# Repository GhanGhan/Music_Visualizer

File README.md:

# Overview      
The device receives an audio signal from a 3.5mm jack (i.e. a headphone jack) that is connected to any analog sound source. The audio signal is then separated into the **7 music frequency ranges** and their respective volumes' are then **displayed on 10 LED's using a decibel scale.**
The brightness of the LEDs and the maximum value of the decibal scale can be adjusted by the user by turning the potentiometers located at the bottom of the PCB shown in *Figure 1*!

***Figure 1: 3D View***
<!---
Hello world

<figure>
   
   <figcaption>**Figure 1: 3D View of Music Visualizer**</figcaption>
</figure>
--->

# Table of Contents
1. Summary of Functionaity
2. Operation Videos
3. Contained in Respository
4. Repository Structure
5. Folder & Design File Explanation
6. Generate Files for Fabrication
7. Current Issues
8. License
9. Acknowledgements

# Summary of Functionality
- Can change input source to a male or female jack using a slide switch as shown in *Figure 2*
- Can safely handle a differential input voltage signal of up to 32V
- Uses 6th order 60dB/decade active Butterworth filters to segment the signal into 7 spectrums
- Both the brightness of the LEDs and maximum scale voltage can be changed using logarithmic potentiometers
   - ** Due to how signal is processed by the filters, the maximum value of the volume scale is 3.5V
- 10 LEDS are used to display the volume of each spectrum as a percentage of the max value of the volume scale
   - 4 Blue LEDs     [4% : 12%]
   - 3 Yellow LEDS   [12% : 35%]
   - 3 Red LEDS      [35% : 100%]

***Figure 2: Block Diagaram of Signal, Power and Control Flow***

# Contained in Repository
- Spice design files (made using LTSpice)
- Schematic Capture and PCB layout (designed in KiCAD)
- Bill-of-Materials BOM
- Other important documents:
   - Sound characterization
   - Measured Frequency response
   - Docs related to properties of critical electrical components

# Operation Videos

# Repository Structure
```
├── Documents
│   ├── BOM_Final.xlsx
│   ├── LED Driver IC.xlsx
│   ├── MaxIoOfEachFilterStage.xlsx
│   ├── Measured_Frequency_Response.xlsx
│   ├── Sound_Characterization.xlsx
│   └── Trace width vs current.xlsx
├── Schematic_PCB/Music_Visualizer
│   ├── Music_Visualizer-backups
│   ├── Project Library
│   │   ├── Coloured_LEDs
│   │   │   ├── LED D5 - Blue_cutted.step
│   │   │   ├── LED D5 - Red_cutted.step
│   │   │   └── LED D5 - Yellow_cutted.step
│   │   ├── DC_Power_Jack
│   │   │   ├── CUI_DEVICES_PJ-079BH.step
│   │   │   ├── CUI_DEVICES.kicad_mod
│   │   │   └── PJ-079BH.lib
│   │   ├── Female_Audio_Jack
│   │   │   └── SJ-3523-SMT-TR--3DModel-STEP-56544.step
│   │   ├── LM3915_LED_Driver
│   │   │   └── LM3915N-1.lib
│   │   ├── Linear_Voltage_Regulator
│   │   │   ├── DIP794W45P254L959H508Q8.kicad_mod
│   │   │   └── LT1054IPE4.step
│   │   ├── PTV09A_Pot_Vertical
│   │   │   ├── PTV09.kicad_mod
│   │   │   └── PTV09A-4225F-B104.step
│   │   ├── PW_On_Off_Switch
│   │   │   ├── E-SWITCH_RR511D1121.kicad_mod
│   │   │   └── RR511D1121.step
│   │   ├── Slide_Switch
│   │   │   ├── OS102011MS2QN1.step
│   │   │   └── SW_OS102011MS2QN1.kicad_mod
│   │   ├── License.txt
│   │   └── how-to-import.htm
│   ├── Music_Visualizer.csv
│   ├── Music_Visualizer.kicad_pcb
│   ├── Music_Visualizer.kicad_prl
│   ├── Music_Visualizer.kicad_pro
│   ├── Music_Visualizer.kicad_sch
│   ├── Music_Visualizer.wbk
│   ├── Music_Visualizer.xml
│   ├── Power.kicad_sch
│   ├── fp-info-cache
│   ├── fp-lib-table
│   └── sym-lib-table
└── Simulated Circuits
    ├── Entire_Circuit 
    │   ├── Full_Visualizer.asc
    │   └── LM324.txt
    ├── Filters_With_LED_Drivers
    │   ├── FinalBassFilterWithLEDDriver.asc
    │   ├── FinalBrillianceFilterWithLEDDriver.asc
    │   ├── FinalLowMidrangeWithLEDDriver.asc
    │   ├── FinalMidrangeFilterWithLEDDriver.asc
    │   ├── FinalPresenceFilterWithLEDDriver.asc
    │   ├── FinalSubBassFilterWithLEDDriver.asc
    │   ├── FinalUpperMidrangeFilterWithLEDDriver.asc
    │   └── LM324.txt
    ├── LED_Driving
    │   ├── LM3915_Base_Circuit.asc
    │   ├── LM3915_Chain.asc
    │   ├── RhiControl_LTC1250.asc
    │   └── Voltage_Follower_Replacement.asc
    ├── Power
    │   ├── LT1054_Inverter_and_regulator.asc
    │   └── Reverse_Voltage_Protection.asc
    └── Spectrum_Filters
        ├── Final_Filters
        │   ├── FinalBassFilterBuf.asc
        │   ├── FinalBrillianceFilterBuf.asc
        │   ├── FinalLowMidrangeBuf.asc
        │   ├── FinalMidrangeFilterBuf.asc
        │   ├── FinalPresenceFilterBuf.asc
        │   ├── FinalSubBassFilterBuf.asc
        │   ├── FinalUpperMidrangeFilterBuf.asc
        │   └── LM324.txt
        ├── Ideal_Filters
        │   ├── BassFilterSK.asc
        │   ├── BrillianceFilterSK.asc
        │   ├── LowMidrangeSK.asc
        │   ├── MidrangeFilterSK.asc
        │   ├── PresenceFilterSK.asc
        │   ├── SubBassFilterSK.asc
        │   └── UpperMidrangeFilterSK.asc
        └── JsonFiles
            ├── Bass Filter.asc
            ├── Brilliance Filter.asc
            ├── Low-Midrange.asc
            ├── Midrange Filter.asc
            ├── Presence Filter.asc
            ├── Sub-Bass Filter.asc
            └── Upper-MidrangeFilter.asc
  ```
# Folder & Design File Explanation
## Documents
- **BOM_Final:** The project Bill-Of-Materials (BOM)
   - Shows all the components that were used, the quantity of each, the prices, model number and where they were sourced from
- **LED Driver IC:** Comparison of the simulated characteristics and values found from breadboarding
- **MaxIoOfEachFilterStage:** Maximum possible current being output by each op-amp of each stage of every filter
- **Sound Characterization:** Shows voltages that were outputted from the audio jack the device was tested on, bandwidth and corner frequency of each spectrum, and steps of the volume-meter
## Schematic_PCB\Music Visualizer (KiCad Folder)
- **Project_Library:** Contains nesseccary .step files (3D models), .lib files (schematic symbols) and/or .kicad_mod files (PCB footprint)  of the DC power jack, female audio jack, LED driver, -5V Inverter & Regulator, potentiometer, On/Off rocker switch switch and slide switch.
    - If any of the file types for any of the circuit elements is not included in the associated sub-folder of the 'Project Library then it is provided by the programs 'Global Library'.
- **Music_Visualizer.kicad_pcb:** PCB layout file for the entire project.
- **Music_Visualizer.kicad_sch:** Main schematic layout file.
    - Contains all 7 frequency spectrums based on the spice files in Simulated_Circuits\Spectrum_Filter\Final_Filter folder.
    - Contains the Audio input circuit (male and female connections where a slide switch is used to choose one or the other), the mounting holes, and op amp bypass capacitors.
    - Contains the Power.kicad_sch and LED_driver.kicad_sch schematics as well
    - **Power.kicad_sch:** Contians circuit for the the +5V regulator, circuit to connect to external power supply with with reverse voltage protection  and -5V Inverter/Regulator as shown in *Figure 3*, the latter 2 are based on the spice files in Simulatd_Circuits\Power.

***Figure 3: 9V & +/-5V Power Circuitry***

    - **Led_Driver.kicad_sch:** Contains the 7 LED drivers, LED brightness control and Rhi-Value Control Circuit based on the spice files in LED_Driving folder.
- **Music_Visualizer.kicad_pro:** Music Visualizer KiCad File.  When clicked it opens up a directory that allows you to access the PCB layout file and schematic layout file.
- Rest of the files are either self explanatory of support files for the KiCad program
## Simulated_Circuits
- **Entire Circuit\Full_Visualizer.asc:** A spice file that contains the 7 spectrum filters being driven by the input signal that contains a frequency from each of the spectrums.  Each of the filters is driving one of the ICs in the LM3915_Chain circuit.  Voltage dividers are used in place of potentiometers to model how turning their knobs allows for control of the LED brightness and scale of the volumeter.
    - **LM324.txt:** A text file that contains the 'macromodel' of the LM324 operational amplifier, allowing it to be used in spice files
- **Filters_With_LED_Drivers:** Contains a spice file for every spectrum filter that driving an LM3915_Base_Circuit.  Also contains an LM324.txt file.
- **LED_Driving:**
    - **LM3915_Base_Circuit.asc:** Contains an LM3915 (the led driver) IC connected to 10 LEDs as shown in *Figure 4*.  The IC is driven by a sinusoidal voltage source.  **Vref (Current reference pin)** is used to set the diode current to about 18mA using a grounded 674 ohm resistor.  It is powered by 9V, and **Vrhi (high-input reference-voltage)** is set to 3.5V.

***Figure 4: LED Driving Circuit Prototype***

    - **LM3915_Chain.asc:** Contains 7 LM3915_Base circuits all driven by the same input AC voltage and high-input reference voltage.  Instead of ground, the 674 ohm resistor of each LM3915_Base circuit is connected to a grounded 10kohm potentiometer.  Changing the resistance of the potentiometer allows one to adjust the current going through the LEDs of all of the LED drivers.
    - **RhiControl_LTC1250.asc:** Connects to the high-input reference voltage pin (*Rhi in Figure 4*) of the LED driver IC as shown in *Figure 5*.  R1 and R2 act as a potentiometer. A voltage follower is appended to the ouput of the 'potentiometer' because the average load voltage of the Vrhi pin is about 17.5kohm, when there are in parallel the equivalent reisistance is about 2.5kohm.  The voltage follower ensures that the voltage at the pins is is the same value as the output of the potentiometer.  This particular op-amp was chosen because it has a max input offset voltage of < |10uV|, this means that the voltage at the pin will always be within 10uV of the desired voltage.

***Figure 5: Volume Scale Range Control Circuit***
  
    - **Voltage_Follower_Replacement.asc:**  This is a common-collector circuit, a single transistor implementation of a current follower.  The 2N2222 transistor is used to replace the LTC1250 op-amp because it shorted the -5 and +5 terminals that it was being powered from.
- **Spectrum_Filters:**
    - **Final_Filters:** Folder contains the final filter design for the 7 spectrum filters; Sub-Bass, Bass, Low-Midrange, Midrange, Upper-Midrange, Presence and Brilliance.  Each filter is prepended with a voltage buffer to isolate themselves from the signal source.  This way the impedances of the filters do not affect each other.  Each filter also has a high-pass filter appended to it to prevent unintented activation of the LED driver due to the input-offset voltage of the LM324 op amps which can be as high as 7mV.  *Figure 6* displays the Sub-Bass filters, all of the spectrum filters have the same topology.
  
***Figure 6: Complete Sub-Base Filter**

         - Also the resistor values in the final design are slightly different from the "ideal version".  This is because those resistances need at least two resistors in series or parallel to be realized.  The nominal resistor values choses for the final design are within 1.5% of the ideal value.  It was determined that this did not have a significant effect on the frequency response. 
    - **Ideal_Filters:** Folder contains design for idealized implementation of the 7 spectrum filters.  In these LTSpice files ideal op-amps are being used and all of the resistor values match the values provided from the Analog Filter Wizard.
    - **JsonFiles:** The spectrum filters were designed using Analog Devices 'Analog Filter Wizard'.  Once you've inputted the specifications "Passband gain, corner frequency, bandwidth, stopband, center frequency, stages etc."  These are the saved specification files of the Analog filter Wizard for each filter.
         - The center frequency saved in these files are different from the actual center frequency of the filters because (for unidentified reasons) when the correct center frequency was inputted to wrong corner frequencies were outputed.  The center frequency contained in these files gives filters with the correct corner frequencies.

# Generate Files for Fabrication
- If you want to generate the Gerber and Drill files so that the project can be fabricated by a JLCPCB, follow the steps of this website: https://jlcpcb.com/help/article/16-How-to-generate-Gerber-and-Drill-files-in-KiCad-6

# Current Issues
- The last stage of the sub-bass filter generates a power 343Hz wave on its own that is so powerful it activates all of the associated LEDS.  
- The LT1054 op amp shorts the +5 and -5 power rails together and destroys itself in the process.  The is why it was replaced with a Common Collector circuit.

# License
- 
- This project is licensed under the [Creative Commons Attribution 3.0 Unported License](https://creativecommons.org/licenses/by/3.0/).
  
# Acknoledgments
- I would like to thank Snap EDA for providing me with the necessary step, kicad_mod and lib files.
- I would like to thank the YouTube Channel "Phil's Lab" for making videos that allowed me to easily learn to use KiCad 6.

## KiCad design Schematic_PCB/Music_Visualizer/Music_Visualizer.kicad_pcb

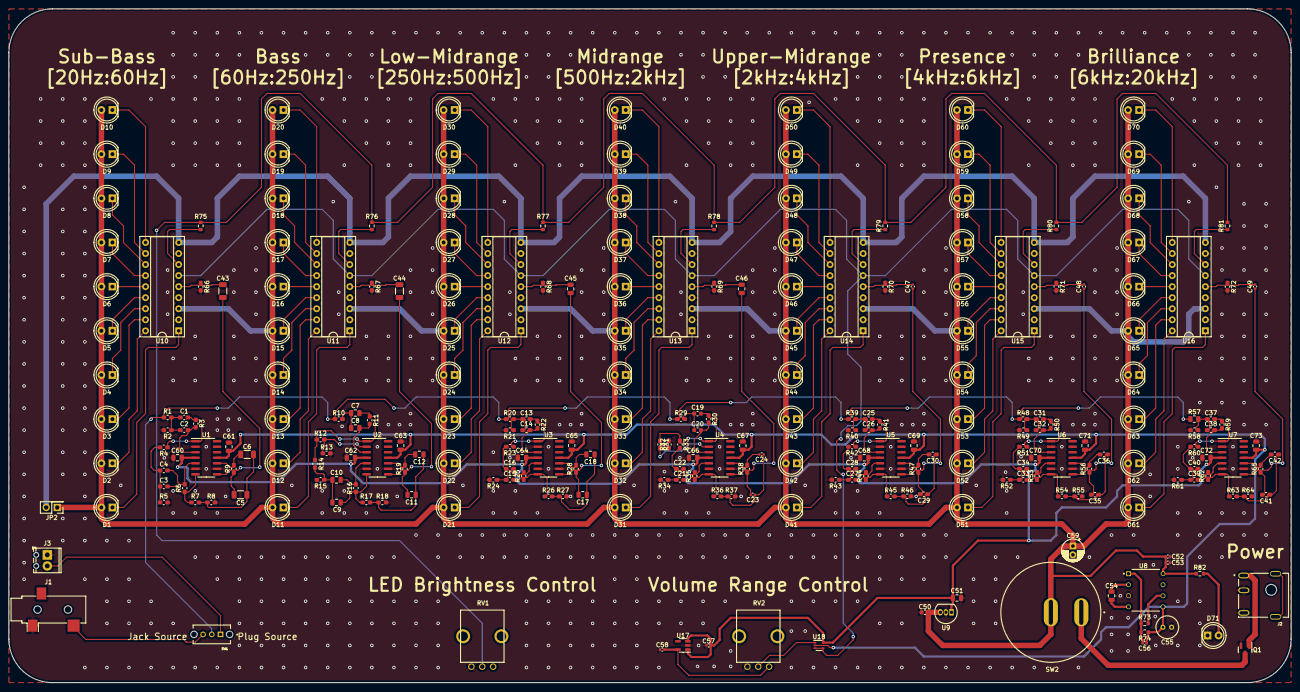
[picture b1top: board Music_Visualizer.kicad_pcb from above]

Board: 2 copper layers, 295.0 x 155.0 mm, 253 parts (0 on the bottom side), 169 nets.

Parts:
C1, C2: 47n; C_0603_1608Metric_Pad1.08x0.95mm_HandSolder
C3, C4: 27n; C_0603_1608Metric_Pad1.08x0.95mm_HandSolder
C5, C6: 75n; C_1206_3216Metric
C7, C8: 13n; C_0805_2012Metric
C9, C10: 6.8n; C_0805_2012Metric
C11, C12: 24n; C_0805_2012Metric
C13, C14: 4.7n; C_0603_1608Metric_Pad1.08x0.95mm_HandSolder
C15, C16: 3.3n; C_0603_1608Metric_Pad1.08x0.95mm_HandSolder
C17, C18: 6.2n; C_0805_2012Metric
C19, C20: 1.6n; C_0603_1608Metric
C21, C22, C25, C26, C27, C28, C29, C30, C31, C32, C33, C34, C35, C36, C37, C38, C39, C40, C41, C42: 1n; C_0603_1608Metric_Pad1.08x0.95mm_HandSolder
C23, C24: 3n; C_0402_1005Metric
C43, C44: 100u; C_1206_3216Metric
C45, C46, C54: 10u; C_0805_2012Metric
C47, C48, C49, C52, C53, C57, C58: 1u; C_0402_1005Metric
C50: 0.33uF; C_0603_1608Metric
C51, C60, C61, C62, C63, C64, C65, C66, C67, C68, C69, C70, C71, C72, C73: 0.1uF; C_0805_2012Metric
C55: 100u; C_Radial_D5.0mm_H5.0mm_P2.00mm
C56: 0.002u; C_0402_1005Metric
C59: 10u; CP_Radial_D5.0mm_P2.00mm
D1, D2, D3, D4, D5, D6, D7, D8, D9, D10, D11, D12, D13, D14, D15, D16, D17, D18, D19, D20, D21, D22, D23, D24, D25, D26, D27, D28, D29, D30, D31, D32, D33, D34, D35, D36, D37, D38, D39, D40, D41, D42, D43, D44, D45, D46, D47, D48, D49, D50, D51, D52, D53, D54, D55, D56, D57, D58, D59, D60, D61, D62, D63, D64, D65, D66, D67, D68, D69, D70, D71: LED; LED_D5.0mm
J1: AudioJack3; Jack_3.5mm_CUI_SJ-3523-SMT_Horizontal
J2: PJ-079BH; CUI_PJ-079BH
J3: Screw_Terminal_01x02; TerminalBlock_Phoenix_MPT-0,5-2-2.54_1x02_P2.54mm_Horizontal
JP2: Jumper_2_Open; PinHeader_2x01_P2.54mm_Vertical
Q1: DMP2123LQ-7; SOT-23
R1: 84.5k; C_0603_1608Metric_Pad1.08x0.95mm_HandSolder
R2, R41, R50: 160k; C_0603_1608Metric_Pad1.08x0.95mm_HandSolder
R3: 169k; C_0603_1608Metric_Pad1.08x0.95mm_HandSolder
R4, R11, R65: 90.9k; C_0603_1608Metric_Pad1.08x0.95mm_HandSolder
R5, R62: 37.4k; C_0603_1608Metric_Pad1.08x0.95mm_HandSolder
R6: 402k; C_0603_1608Metric_Pad1.08x0.95mm_HandSolder
R7: 86.6k; C_0603_1608Metric_Pad1.08x0.95mm_HandSolder
R8: 35.7k; C_0603_1608Metric_Pad1.08x0.95mm_HandSolder
R9: 390k; C_0603_1608Metric_Pad1.08x0.95mm_HandSolder
R10: 110k; C_0603_1608Metric_Pad1.08x0.95mm_HandSolder
R12: 162k; C_0603_1608Metric_Pad1.08x0.95mm_HandSolder
R13: 118k; C_0603_1608Metric_Pad1.08x0.95mm_HandSolder
R14: 63.4k; C_0603_1608Metric_Pad1.08x0.95mm_HandSolder
R15: 62k; C_0603_1608Metric_Pad1.08x0.95mm_HandSolder
R16: 309k; C_0603_1608Metric_Pad1.08x0.95mm_HandSolder
R17: 68k; C_0603_1608Metric_Pad1.08x0.95mm_HandSolder
R18, R31, R36, R51: 66.5k; C_0603_1608Metric_Pad1.08x0.95mm_HandSolder
R19: 332k; C_0603_1608Metric_Pad1.08x0.95mm_HandSolder
R20: 137k; C_0603_1608Metric_Pad1.08x0.95mm_HandSolder
R21: 45.3k; C_0603_1608Metric_Pad1.08x0.95mm_HandSolder
R22, R35, R53: 270k; C_0603_1608Metric_Pad1.08x0.95mm_HandSolder
R23: 143k; C_0603_1608Metric_Pad1.08x0.95mm_HandSolder
R24: 19.1k; C_0603_1608Metric_Pad1.08x0.95mm_HandSolder
R25: 590k; C_0603_1608Metric_Pad1.08x0.95mm_HandSolder
R26: 140k; C_0603_1608Metric_Pad1.08x0.95mm_HandSolder
R27: 18.7k; C_0603_1608Metric_Pad1.08x0.95mm_HandSolder
R28: 576k; C_0603_1608Metric_Pad1.08x0.95mm_HandSolder
R29, R30: 100k; C_0603_1608Metric_Pad1.08x0.95mm_HandSolder
R32: 33.2k; C_0603_1608Metric_Pad1.08x0.95mm_HandSolder
R33: 56k; C_0603_1608Metric_Pad1.08x0.95mm_HandSolder
R34, R58: 48.7k; C_0603_1608Metric_Pad1.08x0.95mm_HandSolder
R37: 57.6k; C_0603_1608Metric_Pad1.08x0.95mm_HandSolder
R38: 324k; C_0603_1608Metric_Pad1.08x0.95mm_HandSolder
R39, R48: 78.7k; C_0603_1608Metric_Pad1.08x0.95mm_HandSolder
R40: 26.7k; C_0603_1608Metric_Pad1.08x0.95mm_HandSolder
R42: 59k; C_0603_1608Metric_Pad1.08x0.95mm_HandSolder
R43: 7.87k; C_0603_1608Metric_Pad1.08x0.95mm_HandSolder
R44: 243k; C_0603_1608Metric_Pad1.08x0.95mm_HandSolder
R45: 107k; C_0603_1608Metric_Pad1.08x0.95mm_HandSolder
R46: 14.7k; C_0603_1608Metric_Pad1.08x0.95mm_HandSolder
R47: 453k; C_0603_1608Metric_Pad1.08x0.95mm_HandSolder
R49: 7.32k; C_0603_1608Metric_Pad1.08x0.95mm_HandSolder
R52: 2.87k; C_0603_1608Metric_Pad1.08x0.95mm_HandSolder
R54: 95.3k; C_0603_1608Metric_Pad1.08x0.95mm_HandSolder
R55: 4.02k; C_0603_1608Metric_Pad1.08x0.95mm_HandSolder
R56: 383k; C_0603_1608Metric_Pad1.08x0.95mm_HandSolder
R57: 11.5k; R_0805_2012Metric
R59: 22.6k; C_0603_1608Metric_Pad1.08x0.95mm_HandSolder
R60: 8.06k; C_0603_1608Metric_Pad1.08x0.95mm_HandSolder
R61: 4.32k; C_0603_1608Metric_Pad1.08x0.95mm_HandSolder
R63: 19.6k; C_0603_1608Metric_Pad1.08x0.95mm_HandSolder
R64: 10.7k; C_0603_1608Metric_Pad1.08x0.95mm_HandSolder
R66, R67, R68, R69, R70, R71, R72: 1k; C_0603_1608Metric_Pad1.08x0.95mm_HandSolder
R73: 20k; R_0603_1608Metric
R74: 102k; R_0603_1608Metric
R75, R76, R77, R78, R79, R80, R81: 680; R_0603_1608Metric
R82: 330; R_0603_1608Metric
RV1: 10k_LED_Brightness_Pot; PTV09
RV2: 5k_Rhi_Adjuster; PTV09
SW1: SW_SPDT; SW_OS102011MS2QN1
SW2: SW_SPST; E-SWITCH_RR511D1121
U1, U2, U3, U4, U5, U6, U7: LM324; SOIC-14_3.9x8.7mm_P1.27mm
U8: LT1054; DIP794W45P254L959H508Q8
U9: MC78L05_TO92; TO-92_Inline
U10, U11, U12, U13, U14, U15, U16: LM3915N-1; DIP-18_W7.62mm_Socket
U17: NCP161ASN350T1G; SOT-23-5
U18: NCS333ASQ3T2G; SOT-353_SC-70-5

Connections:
+5V: C51.1, C57.1, C60.2, C62.2, C64.2, C66.2, C68.2, C70.2, C72.2, U1.4 (V+), U2.4 (V+), U3.4 (V+), U4.4 (V+), U5.4 (V+), U6.4 (V+), U7.4 (V+), U9.1 (VO), U17.1 (IN), U17.3 (EN), U18.5 (V+)
+9V: C50.1, C52.1, C53.1, C59.1, D1.2 (A), D2.2 (A), D3.2 (A), D4.2 (A), D5.2 (A), D6.2 (A), D7.2 (A), D8.2 (A), D9.2 (A), D10.2 (A), D11.2 (A), D12.2 (A), D13.2 (A), D14.2 (A), D15.2 (A), D16.2 (A), D17.2 (A), D18.2 (A), D19.2 (A), D20.2 (A), D21.2 (A), D22.2 (A), D23.2 (A), D24.2 (A), D25.2 (A), D26.2 (A), D27.2 (A), D28.2 (A), D29.2 (A), D30.2 (A), D31.2 (A), D32.2 (A), D33.2 (A), D34.2 (A), D35.2 (A), D36.2 (A), D37.2 (A), D38.2 (A), D39.2 (A), D40.2 (A), D41.2 (A), D42.2 (A), D43.2 (A), D44.2 (A), D45.2 (A), D46.2 (A), D47.2 (A), D48.2 (A), D49.2 (A), D50.2 (A), D51.2 (A), D52.2 (A), D53.2 (A), D54.2 (A), D55.2 (A), D56.2 (A), D57.2 (A), D58.2 (A), D59.2 (A), D60.2 (A), D61.2 (A), D62.2 (A), D63.2 (A), D64.2 (A), D65.2 (A), D66.2 (A), D67.2 (A), D68.2 (A), D69.2 (A), D70.2 (A), JP2.1 (A), R82.1, SW2.2 (B), U8.8 (V+), U9.3 (VI), U10.3 (V+), U11.3 (V+), U12.3 (V+), U13.3 (V+), U14.3 (V+), U15.3 (V+), U16.3 (V+)
-5V: C55.1, C56.1, C61.1, C63.1, C65.1, C67.1, C69.1, C71.1, C73.1, R74.1, U1.11 (V-), U2.11 (V-), U3.11 (V-), U4.11 (V-), U5.11 (V-), U6.11 (V-), U7.11 (V-), U8.5 (-VOUT), U18.2 (V-)
/Power/Power: J2.1, Q1.1 (D)
/Vsig_female: J1.T, SW1.3 (C)
/Vsig_male: J3.2, SW1.1 (A)
GND: C50.2, C51.2, C52.2, C53.2, C55.2, C57.2, C58.2, C59.2, C60.1, C61.2, C62.1, C63.2, C64.1, C65.2, C66.1, C67.2, C68.1, C69.2, C70.1, C71.2, C72.1, C73.2, D71.1 (K), J1.S, J2.2, J2.3, J3.1, Q1.2 (G), R2.2, R5.2, R8.2, R13.2, R15.2, R18.2, R21.2, R24.2, R27.2, R32.2, R34.2, R37.2, R40.2, R43.2, R46.2, R49.2, R52.2, R55.2, R58.2, R61.2, R64.2, R66.2, R67.2, R68.2, R69.2, R70.2, R71.2, R72.2, RV1.1, RV2.1, U1.2 (-), U1.6 (-), U1.9 (-), U2.6 (-), U2.9 (-), U3.2 (-), U3.6 (-), U3.9 (-), U4.6 (-), U4.9 (-), U5.2 (-), U5.6 (-), U5.9 (-), U6.2 (-), U6.6 (-), U6.9 (-), U7.2 (-), U7.6 (-), U7.9 (-), U8.3 (GND), U9.2 (GND), U10.2 (V-), U10.4 (RLO), U10.8 (REF_ADJ), U11.2 (V-), U11.4 (RLO), U11.8 (REF_ADJ), U12.2 (V-), U12.4 (RLO), U12.8 (REF_ADJ), U13.2 (V-), U13.4 (RLO), U13.8 (REF_ADJ), U14.2 (V-), U14.4 (RLO), U14.8 (REF_ADJ), U15.2 (V-), U15.4 (RLO), U15.8 (REF_ADJ), U16.2 (V-), U16.4 (RLO), U16.8 (REF_ADJ), U17.2 (GND)
LED_Brightness_Control: R75.2, R76.2, R77.2, R78.2, R79.2, R80.2, R81.2, RV1.2
Mode: JP2.2 (B), U10.9 (MODE), U11.9 (MODE), U12.9 (MODE), U13.9 (MODE), U14.9 (MODE), U15.9 (MODE), U16.9 (MODE)
unnamed: C1.1, C2.1, R1.2, R2.1
unnamed: C1.2, R3.1, R4.1, U1.1
unnamed: C2.2, R3.2, U1.3 (+)
unnamed: C3.1, C4.1, R4.2, R5.1
unnamed: C3.2, R6.1, R7.1, U1.7
unnamed: C4.2, R6.2, U1.5 (+)
unnamed: C5.1, C6.1, R7.2, R8.1
unnamed: C6.2, R9.2, U1.10 (+)
unnamed: C7.1, C8.1, R10.2
unnamed: C7.2, R11.1, R12.1, R14.1, U2.1
unnamed: C8.2, R11.2, U2.3 (+)
unnamed: C9.2, R16.1, R17.1, U2.7
unnamed: C9.1, C10.1, R14.2, R15.1
unnamed: C10.2, R16.2, U2.5 (+)
unnamed: C11.1, C12.1, R17.2, R18.1
unnamed: C11.2, C44.1, R19.1, U2.8
unnamed: C12.2, R19.2, U2.10 (+)
unnamed: C13.1, C14.1, R20.2, R21.1
unnamed: C13.2, R22.1, R23.1, U3.1
unnamed: C14.2, R22.2, U3.3 (+)
unnamed: C15.1, C16.1, R23.2, R24.1
unnamed: C15.2, R25.1, R26.1, U3.7
unnamed: C16.2, R25.2, U3.5 (+)
unnamed: C17.1, C18.1, R26.2, R27.1
unnamed: C17.2, C45.1, R28.1, U3.8
unnamed: C18.2, R28.2, U3.10 (+)
unnamed: C19.1, C20.1, R29.2
unnamed: C19.2, R30.1, R31.1, R33.1, U4.1
unnamed: C20.2, R30.2, U4.3 (+)
unnamed: C21.1, C22.1, R33.2, R34.1
unnamed: C21.2, R35.1, R36.1, U4.7
unnamed: C22.2, R35.2, U4.5 (+)
unnamed: C23.1, C24.1, R36.2, R37.1
unnamed: C23.2, C46.1, R38.1, U4.8
unnamed: C24.2, R38.2, U4.10 (+)
unnamed: C25.1, C26.1, R39.2, R40.1
unnamed: C25.2, R41.1, R42.1, U5.1
unnamed: C26.2, R41.2, U5.3 (+)
unnamed: C27.1, C28.1, R42.2, R43.1
unnamed: C27.2, R44.1, R45.1, U5.7
unnamed: C28.2, R44.2, U5.5 (+)
unnamed: C29.1, C30.1, R45.2, R46.1
unnamed: C29.2, C47.1, R47.1, U5.8
unnamed: C30.2, R47.2, U5.10 (+)
unnamed: C31.1, C32.1, R48.2, R49.1
unnamed: C31.2, R50.1, R51.1, U6.1
unnamed: C32.2, R50.2, U6.3 (+)
unnamed: C33.1, C34.1, R51.2, R52.1
unnamed: C33.2, R53.1, R54.1, U6.7
unnamed: C34.2, R53.2, U6.5 (+)
unnamed: C35.1, C36.1, R54.2, R55.1
unnamed: C35.2, C48.1, R56.1, U6.8
unnamed: C36.2, R56.2, U6.10 (+)
unnamed: C37.1, C38.1, R57.2, R58.1
unnamed: C37.2, R59.1, R60.1, U7.1
unnamed: C38.2, R59.2, U7.3 (+)
unnamed: C39.1, C40.1, R60.2, R61.1
unnamed: C39.2, R62.1, R63.1, U7.7
unnamed: C40.2, R62.2, U7.5 (+)
unnamed: C41.1, C42.1, R63.2, R64.1
unnamed: C41.2, C49.1, R65.1, U7.8
unnamed: C42.2, R65.2, U7.10 (+)
unnamed: C5.2, C43.1, R9.1, U1.8
unnamed: C54.1, U8.2 (CAP+)
unnamed: C54.2, U8.4 (CAP-)
unnamed: C56.2, R73.1, R74.2, U8.1 (FB/SHDN)
unnamed: C58.1, RV2.3, U17.5 (OUT)
unnamed: D1.1 (K), U10.1 (LED1_K)
unnamed: D2.1 (K), U10.18 (LED2_K)
unnamed: D3.1 (K), U10.17 (LED3_K)
unnamed: D4.1 (K), U10.16 (LED4_K)
unnamed: D5.1 (K), U10.15 (LED5_K)
unnamed: D6.1 (K), U10.14 (LED6_K)
unnamed: D7.1 (K), U10.13 (LED7_K)
unnamed: D8.1 (K), U10.12 (LED8_K)
unnamed: D9.1 (K), U10.11 (LED9_K)
unnamed: D10.1 (K), U10.10 (LED10_K)
unnamed: D11.1 (K), U11.1 (LED1_K)
unnamed: D12.1 (K), U11.18 (LED2_K)
unnamed: D13.1 (K), U11.17 (LED3_K)
unnamed: D14.1 (K), U11.16 (LED4_K)
unnamed: D15.1 (K), U11.15 (LED5_K)
unnamed: D16.1 (K), U11.14 (LED6_K)
unnamed: D17.1 (K), U11.13 (LED7_K)
unnamed: D18.1 (K), U11.12 (LED8_K)
unnamed: D19.1 (K), U11.11 (LED9_K)
unnamed: D20.1 (K), U11.10 (LED10_K)
unnamed: D21.1 (K), U12.1 (LED1_K)
unnamed: D22.1 (K), U12.18 (LED2_K)
unnamed: D23.1 (K), U12.17 (LED3_K)
unnamed: D24.1 (K), U12.16 (LED4_K)
unnamed: D25.1 (K), U12.15 (LED5_K)
unnamed: D26.1 (K), U12.14 (LED6_K)
unnamed: D27.1 (K), U12.13 (LED7_K)
unnamed: D28.1 (K), U12.12 (LED8_K)
unnamed: D29.1 (K), U12.11 (LED9_K)
unnamed: D30.1 (K), U12.10 (LED10_K)
unnamed: D31.1 (K), U13.1 (LED1_K)
unnamed: D32.1 (K), U13.18 (LED2_K)
unnamed: D33.1 (K), U13.17 (LED3_K)
unnamed: D34.1 (K), U13.16 (LED4_K)
unnamed: D35.1 (K), U13.15 (LED5_K)
unnamed: D36.1 (K), U13.14 (LED6_K)
unnamed: D37.1 (K), U13.13 (LED7_K)
unnamed: D38.1 (K), U13.12 (LED8_K)
unnamed: D39.1 (K), U13.11 (LED9_K)
unnamed: D40.1 (K), U13.10 (LED10_K)
unnamed: D41.1 (K), U14.1 (LED1_K)
unnamed: D42.1 (K), U14.18 (LED2_K)
unnamed: D43.1 (K), U14.17 (LED3_K)
unnamed: D44.1 (K), U14.16 (LED4_K)
unnamed: D45.1 (K), U14.15 (LED5_K)
unnamed: D46.1 (K), U14.14 (LED6_K)
unnamed: D47.1 (K), U14.13 (LED7_K)
unnamed: D48.1 (K), U14.12 (LED8_K)
unnamed: D49.1 (K), U14.11 (LED9_K)
unnamed: D50.1 (K), U14.10 (LED10_K)
unnamed: D51.1 (K), U15.1 (LED1_K)
unnamed: D52.1 (K), U15.18 (LED2_K)
unnamed: D53.1 (K), U15.17 (LED3_K)
unnamed: D54.1 (K), U15.16 (LED4_K)
unnamed: D55.1 (K), U15.15 (LED5_K)
unnamed: D56.1 (K), U15.14 (LED6_K)
unnamed: D57.1 (K), U15.13 (LED7_K)
unnamed: D58.1 (K), U15.12 (LED8_K)
unnamed: D59.1 (K), U15.11 (LED9_K)
unnamed: D60.1 (K), U15.10 (LED10_K)
unnamed: D61.1 (K), U16.1 (LED1_K)
unnamed: D62.1 (K), U16.18 (LED2_K)
unnamed: D63.1 (K), U16.17 (LED3_K)
unnamed: D64.1 (K), U16.16 (LED4_K)
unnamed: D65.1 (K), U16.15 (LED5_K)
unnamed: D66.1 (K), U16.14 (LED6_K)
unnamed: D67.1 (K), U16.13 (LED7_K)
unnamed: D68.1 (K), U16.12 (LED8_K)
unnamed: D69.1 (K), U16.11 (LED9_K)
unnamed: D70.1 (K), U16.10 (LED10_K)
unnamed: D71.2 (A), R82.2
unnamed: J2.S1 (SHIELD), J2.S2 (SHIELD)
unnamed: Q1.3 (S), SW2.1 (A)
unnamed: R12.2, R13.1, U2.2 (-)
unnamed: R31.2, R32.1, U4.2 (-)
unnamed: R73.2, U8.6 (VREF)
unnamed: R75.1, U10.7 (REF_OUT)
unnamed: R76.1, U11.7 (REF_OUT)
unnamed: R77.1, U12.7 (REF_OUT)
unnamed: R78.1, U13.7 (REF_OUT)
unnamed: R79.1, U14.7 (REF_OUT)
unnamed: R80.1, U15.7 (REF_OUT)
unnamed: R81.1, U16.7 (REF_OUT)
unnamed: RV2.2, U18.1 (+)
Rhi_Value: U10.6 (RHI), U11.6 (RHI), U12.6 (RHI), U13.6 (RHI), U14.6 (RHI), U15.6 (RHI), U16.6 (RHI), U18.3 (-), U18.4
VBass: C44.2, R67.1, U11.5 (SIG)
VBrilliance: C49.2, R72.1, U16.5 (SIG)
VLowerMidrange: C45.2, R68.1, U12.5 (SIG)
VMidrange: C46.2, R69.1, U13.5 (SIG)
VPresence: C48.2, R71.1, U15.5 (SIG)
VSubBass: C43.2, R66.1, U10.5 (SIG)
VUpperMidrange: C47.2, R70.1, U14.5 (SIG)
Vsig: R1.1, R10.1, R20.1, R29.1, R39.1, R48.1, R57.1, SW1.2 (B)

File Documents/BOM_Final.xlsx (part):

Comment | Designator | Footprint | Quantity | Digi-Key PN | MPN | Price | Total Price | Part Page
47n | C1,C2 | Capacitor_SMD:C_0603_1608Metric_Pad1.08x0.95mm_HandSolder | 2 | 1292-1445-1-ND | 0603B473J250CT | 0.1 | 0.2 | https://www.digikey.ca/en/products/detail/walsin-technology-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
24n | C11,C12 | Capacitor_SMD:C_0805_2012Metric | 2 | 478-10432-1-ND | 08051C243JAT2A | 0.43 | 0.86 | https://www.digikey.ca/en/products/detail/kyocera-avx/08051C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
4.7n | C13,C14 | Capacitor_SMD:C_0603_1608Metric_Pad1.08x0.95mm_HandSolder | 2 | 1292-1440-1-ND | 0603B472J500CT | 0.1 | 0.2 | https://www.digikey.ca/en/products/detail/walsin-technology-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
3.3n | C15,C16 | Capacitor_SMD:C_0603_1608Metric_Pad1.08x0.95mm_HandSolder | 2 | 1292-1521-1-ND | 0603N332J500CT | 0.1 | 0.2 | https://www.digikey.ca/en/products/detail/walsin-technology-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
6.2n | C17,C18 | Capacitor_SMD:C_0805_2012Metric | 2 | 490-1637-1-ND | GRM2195C1H622JA01D | 0.41 | 0.82 | https://www.digikey.ca/en/products/detail/murata-electronics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
1.6n | C19,C20 | Capacitor_SMD:C_0603_1608Metric_Pad1.08x0.95mm_HandSolder | 2 | 490-1456-1-ND | GRM1885C1H162JA01D | 0.18 | 0.36 | https://www.digikey.ca/en/products/detail/murata-electronics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
1n | C21,C22,C25,C26,C27,C28,C29,C30,C31,C32,C33,C34,C35,C36,C37,C38,C41,C42 | Capacitor_SMD:C_0603_1608Metric_Pad1.08x0.95mm_HandSolder | 18 | 1276-1091-1-ND | CL10C102JB8NNNC | 0.1 | 1.8 | https://www.digikey.ca/en/products/detail/samsung-electro-me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
3n | C23,C24 | Capacitor_SMD:C_0603_1608Metric_Pad1.08x0.95mm_HandSolder | 2 | 490-6384-1-ND | GRM1885C1H302JA01D | 0.11 | 0.22 | https://www.digikey.ca/en/products/detail/murata-electronics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
27n | C3,C4 | Capacitor_SMD:C_0603_1608Metric_Pad1.08x0.95mm_HandSolder | 2 | 478-KAF15AR71H273JMTR-ND | KAF15AR71H273JM | 0.18 | 0.36 | https://www.digikey.ca/en/products/detail/kyocera-avx/KAF15A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
820p | C39,C40 | Capacitor_SMD:C_0603_1608Metric_Pad1.08x0.95mm_HandSolder | 2 | 1292-1548-1-ND | 0603N821J500CT | 0.14000000000000001 | 0.28000000000000003 | https://www.digikey.ca/en/products/detail/walsin-technology-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
100u | C43,C44 | Capacitor_SMD:C_1206_3216Metric | 2 | 490-GRM31CD80J107MEA8KCT-ND | GRM31CD80J107MEA8K | 0.56000000000000005 | 1.1200000000000001 | https://www.digikey.ca/en/products/detail/murata-electronics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
10u | C45,C46,C54 | Capacitor_SMD:C_0805_2012Metric | 3 | 1276-1096-1-ND | CL21A106KOQNNNE | 0.14000000000000001 | 0.42000000000000004 | https://www.digikey.ca/en/products/detail/samsung-electro-me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
1u | C47,C48,C49,C52,C53,C57,C58 | Capacitor_SMD:C_0603_1608Metric_Pad1.08x0.95mm_HandSolder | 7 | 311-3485-1-ND | CC0603JRX7R7BB105 | 0.34 | 2.3800000000000003 | https://www.digikey.ca/en/products/detail/yageo/CC0603JRX7R7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
75n | C5,C6 | Capacitor_SMD:C_1206_3216Metric | 2 | 490-6506-1-ND | GRM31C5C1H753JA01L | 0.53 | 1.06 | https://www.digikey.ca/en/products/detail/murata-electronics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
0.33uF | C50 | Capacitor_SMD:C_0603_1608Metric_Pad1.08x0.95mm_HandSolder | 1 | 732-7992-1-ND | 885012206074 | 0.14000000000000001 | 0.14000000000000001 | https://www.digikey.ca/en/products/detail/w%C3%BCrth-elektro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
100u | C55 | Capacitor_THT:C_Radial_D5.0mm_H5.0mm_P2.00mm | 1 | 732-8598-1-ND | 860010372006 | 0.15 | 0.15 | https://www.digikey.ca/en/products/detail/w%C3%BCrth-elektro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
0.002u | C56 | Capacitor_SMD:C_0603_1608Metric_Pad1.08x0.95mm_HandSolder | 1 | 490-GCM1885C1H202JA16DCT-ND | GCM1885C1H202JA16D | 0.1 | 0.1 | https://www.digikey.ca/en/products/detail/murata-electronics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
10u | C59 | Capacitor_THT:CP_Radial_D5.0mm_P2.00mm | 1 | 732-8593-1-ND | 860010372001 | 0.14000000000000001 | 0.14000000000000001 | https://www.digikey.ca/en/products/detail/w%C3%BCrth-elektro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
0.1uF | C51,C60,C61,C62,C63,C64,C65,C66,C67,C68,C69,C70,C71,C72,C73 | Capacitor_SMD:C_0805_2012Metric | 15 | 1276-1099-1-ND | CL21B104KACNNNC | 0.14000000000000001 | 2.1 | https://www.digikey.ca/en/products/detail/samsung-electro-me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
13n | C7,C8 | Capacitor_SMD:C_0805_2012Metric | 2 | 490-12752-1-ND | GRM2195C1H133JA01D | 0.36 | 0.72 | https://www.digikey.ca/en/products/detail/murata-electronics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
6.8n | C9,C10 | Capacitor_SMD:C_0805_2012Metric | 2 | 399-C0805C682J5GEC7210CT-ND | C0805C682J5GEC7210 | 0.36 | 0.72 | https://www.digikey.ca/en/products/detail/kemet/C0805C682J5G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
LED | D1,D2,D3,D4,D5,D6,D7,D8,D9,D10,D11,D12,D13,D14,D15,D16,D17,D18,D19,D20,D21,D22,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 | LED_THT:LED_D5.0mm | 70 | N/A | N/A | 3.3180000000000001E-2 | 2.3226 | https://www.amazon.ca/gp/product/B07N2GVCYZ/ref=ppx_yo_dt_b_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
MountingHole | H1,H2,H3,H4 | MountingHole:MountingHole_3.2mm_M3 | 4 | N/A | N/A | N/A | 0 | N/A
AudioJack3 | J1 | Connector_Audio:Jack_3.5mm_CUI_SJ-3523-SMT_Horizontal | 1 | CP-3523SJCT-ND | SJ-3523-SMT-TR | 1.42 | 1.42 | https://www.digikey.ca/en/products/detail/cui-devices/SJ-352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
PJ-079BH | J2 | CUI_PJ-079BH | 1 | 102-5547-ND | PJ-079BH | 2.19 | 2.19 | https://www.digikey.ca/en/products/detail/cui-devices/PJ-079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
Screw_Terminal_01x02 | J3 | TerminalBlock_Phoenix:TerminalBlock_Phoenix_MPT-0,5-2-2.54_1x02_P2.54mm_Horizon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 | 1 | 952-2262-ND | M20-9990246 | 0.19 | 0.19 | https://www.digikey.ca/en/products/detail/harwin-inc/M20-999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
Jumper_2_Open | JP2 | Connector_PinHeader_2.54mm:PinHeader_2x01_P2.54mm_Vertical | 1 | DMP2123LQ-7DICT-ND | DMP2123LQ-7 | 0.8 | 0.8 | https://www.digikey.ca/en/products/detail/diodes-incorporate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
DMP2123LQ-7 | Q1 | Package_TO_SOT_SMD:SOT-23 | 1 | DMP2123LQ-7DICT-ND | DMP2123LQ-7 | 0.69 | 0.69 | https://www.digikey.ca/en/products/detail/diodes-incorporate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
84.5k | R1 | Resistor_SMD:R_0603_1608Metric_Pad0.98x0.95mm_HandSolder | 1 | 311-84.5KHRCT-ND | RC0603FR-0784K5L | 0.15 | 0.15 | https://www.digikey.ca/en/products/detail/yageo/RC0603FR-078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
110k | R10 | Resistor_SMD:R_0603_1608Metric_Pad0.98x0.95mm_HandSolder | 1 | 311-110KHRCT-ND | RC0603FR-07110KL | 0.15 | 0.15 | https://www.digikey.ca/en/products/detail/yageo/RC0603FR-071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
162k | R12 | Resistor_SMD:R_0603_1608Metric_Pad0.98x0.95mm_HandSolder | 1 | 311-162KHRCT-ND | RC0603FR-07162KL | 0.15 | 0.15 | https://www.digikey.ca/en/products/detail/yageo/RC0603FR-071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
118k | R13 | Resistor_SMD:R_0603_1608Metric_Pad0.98x0.95mm_HandSolder | 1 | 311-118KHRCT-ND | RC0603FR-07118KL | 0.15 | 0.15 | https://www.digikey.ca/en/products/detail/yageo/RC0603FR-071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
63.4k | R14 | Resistor_SMD:R_0603_1608Metric_Pad0.98x0.95mm_HandSolder | 1 | 311-63.4KHRCT-ND | RC0603FR-0763K4L | 0.15 | 0.15 | https://www.digikey.ca/en/products/detail/yageo/RC0603FR-076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
62k | R15 | Resistor_SMD:R_0603_1608Metric_Pad0.98x0.95mm_HandSolder | 1 | 311-62.0KHRCT-ND | RC0603FR-0762KL | 0.15 | 0.15 | https://www.digikey.ca/en/products/detail/yageo/RC0603FR-076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
309k | R16 | Resistor_SMD:R_0603_1608Metric_Pad0.98x0.95mm_HandSolder | 1 | 311-309KHRCT-ND | RC0603FR-07309KL | 0.15 | 0.15 | https://www.digikey.ca/en/products/detail/yageo/RC0603FR-073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
68k | R17 | Resistor_SMD:R_0603_1608Metric_Pad0.98x0.95mm_HandSolder | 1 | 311-68.0KHRCT-ND | RC0603FR-0768KL | 0.15 | 0.15 | https://www.digikey.ca/en/products/detail/yageo/RC0603FR-076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
66.5k | R18,R31,R36,R51 | Resistor_SMD:R_0603_1608Metric_Pad0.98x0.95mm_HandSolder | 1 | 311-66.5KHRCT-ND | RC0603FR-0766K5L | 0.15 | 0.15 | https://www.digikey.ca/en/products/detail/yageo/RC0603FR-076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
332k | R19 | Resistor_SMD:R_0603_1608Metric_Pad0.98x0.95mm_HandSolder | 1 | 311-332KHRCT-ND | RC0603FR-07332KL | 0.15 | 0.15 | https://www.digikey.ca/en/products/detail/yageo/RC0603FR-073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
160k | R2,R41,R50 | Resistor_SMD:R_0603_1608Metric_Pad0.98x0.95mm_HandSolder | 1 | 311-160KHRCT-ND | RC0603FR-07160KL | 0.15 | 0.15 | https://www.digikey.ca/en/products/detail/yageo/RC0603FR-071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
137k | R20 | Resistor_SMD:R_0603_1608Metric_Pad0.98x0.95mm_HandSolder | 1 | 311-137KHRCT-ND | RC0603FR-07137KL | 0.15 | 0.15 | https://www.digikey.ca/en/products/detail/yageo/RC0603FR-071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
45.3k | R21 | Resistor_SMD:R_0603_1608Metric_Pad0.98x0.95mm_HandSolder | 1 | 311-45.3KHRCT-ND | RC0603FR-0745K3L | 0.15 | 0.15 | https://www.digikey.ca/en/products/detail/yageo/RC0603FR-074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

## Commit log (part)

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2022-04-17 Organizded files into descriptive folders
2022-04-17 Add active Butterworth filter desgins from Sub-Bass, Bass, Low-Midrange, Midrange, Upper-Midrange, Presence, and Brilliance frequency spectrums
2022-04-19 Add Compatoro-LED volume ladder schematic, and to the Frequency information spreadsheet - voltages of aux cable at different volumes and sheet showing how volume division will be done
2022-04-19 Use 'real' op amp to succeed Bridge Rectifier
2022-04-21 Add Low-Midrange filter
2022-04-21 Add Midrange filter
2022-04-21 Add Upper-Midrange filter
2022-04-21 Add Presence filter
2022-04-21 Add ReadME
2022-04-21 Add updated ReadME
2022-04-22 Add Rectifiers folder, and add Half-Wave Rectifier Schematic
2022-04-22 Properly connect Vcc and Vee to opamp
2022-04-22 Add Super Diode Half Wave Rectifier, need to use opamp AD8606 to properly simulate
2022-04-23 Add Super Diode Full Wave Rectifier
2022-04-23 Add Precision Full Wave Rectifier
2022-04-23 Connected negative power rail of of opamp to ground instead of Vee, now there is no negative voltage saturation when Vin is negative
2022-04-24 Use bandpass instead of low pass filter to isolate sub-bass frequencies
2022-05-09 Base Circuit for using the LM3915 IC
2022-05-09 Adjusted R2 and Vs to better reflect real world values
2022-05-13 Method to power op-amp using a dual-rail voltage regulator
2022-05-13 Villard Cascade Negative Voltage multiplier will precede a negative voltage regulator that will provide -Vee for op amp circuits
2022-05-15 Corrected and organized spectrum filters and finalized design of negative power source
2022-05-22 Finalized and sourced Resistor values for all filters
2022-05-22 Finalized and sourced Capacitor values for all filters
2022-05-26 Replaced through-hole resistors and capacitors with SMD types, all resisotrs of Case Code (mm) 0603, most caps are Case Code (mm) 0603, a few are 1005, 1608, 2012 and 3216
2022-05-26 Made design to control LED's of all LM3915 ic's from a single potentiometer. Drawback - reference voltage between pin 7 and pin 8 will be between 20mV and 764mV depending on the potentiometer value, 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
2022-06-01 LED Driver IC excel file shows result of varying resistance between pin Ref and ground and grounding pin Adj. Doing so with one LM3915 IC was simulated in Base Circuit version 2, doing so with all 7 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
2022-06-08 Added Case code (mm) and datasheet links for all resistors and capacitors in Sub-bass and Bass filters in the BOM excel file
2022-06-08 Started making schematic of project in KiCad, currently finished drafting the sub-Bass filter with correct footprints
2022-06-08 Added passive components of all filters on one sheet it Bom, component number reflects its ordering in the schematic
2022-06-08 Correct R6 value from 600kohm to 590 kohm
2022-06-08 Added all filters with proper footprints to KiCad Schematic
2022-06-22 Changed pulse frquency, Ton an Rout to better simuluate actual circuit
2022-06-23 Placed all filters on one schematic and tested current drawn from voltage sources, always less than or equal to 9mA
2022-06-23 Component values and outputs for Negative Voltage Multiplier 555 timer
2022-06-23 Corrected polarity of C4 and C5, added voltage node labels
2022-06-23 Sourced all power circuitry
2022-06-24 Updated Full Negative 5V Regulator Circuit with NE555 timer
2022-06-24 Placed all filter and LED driver circuits on one schematic, verified power consumption
2022-06-27 Add Rhi level control sub-circuit, using LM324 and LTC1250 as stand in for the NCS333ASQ3T2G
2022-06-30 Calculate current that is being outputted
2022-06-30 Calculate maximum current being outputted by each Spectrum filter and each stage within them
2022-06-30 Combined each final spectrum filter with high-pass RC filter and LM3915 LED circuit
2022-07-19 Updated Bom, Full Visualizer Circuit, and Circuit for establishing -5 volts
2022-07-21 Added audio signal circuitry
2022-07-21 Finished power circuitry schematic and updated BOM
2022-07-21 Completed and annotated Spectrum filters and power circuitry, and updated BOM
2022-07-22 Finished LED Driver Sub-Circuit and updated BOM
2022-07-22 Start PCB
2022-07-22 intermediary file changes
2022-07-22 Deleted large raw file
2022-07-23 Sourced on_off switch and added on_off switch/indicator circuit
2022-07-25 Got 3D models for all parts, corrected signal voltage to each driver and made outline of PCB
2022-07-25 Formated LEDs, LED drivers and filters in PCB editor
2022-07-25 Labelled necessary subcircuits in the PCB Editor
2022-08-04 Fully connected LEDs and driver ICs to 9V
2022-08-25 Table and chart of trace width vs current
2022-08-25 Added 10 uF polarized smoothing capacitors to LED driver ciruit
2022-08-28 Aligned all subcircuits, routed 9V and power, started routing LEDS
2022-08-28 Finished Routing LEDs
2022-08-28 Finieshed Routing Brightness control, FilterOut and RHigh
2022-08-28 Added 3D model of power port
2022-08-30 Rounded PCB corners
2022-08-30 Added 7th LM324 Quad-op-amp IC to Filter array, updated numbering on all other ICs
2022-09-03 Routed bass and sub-bass
2022-09-20 Added ground pour to top and bottom layers
2022-09-20 Finished Tracing bass filter
2022-09-21 Traced Lower-Midrange Filter
2022-09-21 Finished tracing all of the spectrum filters
2022-09-22 Routed Volume range and LED brightness control
2022-09-22 Added screw port terminal block to connect male audio jack, traceed audio input and header, all nets have now been traced
2022-09-23 Made minor trace position adjustments
2022-09-26 Oriented Component names
2022-10-13 Updated BOM, experimented with some circuit parameters
2022-10-13 Re-oriented Power Indicator circuit
2022-10-13 Added 0.1uF decoupling capacitors to the op-amps on the schematic and placed and traced on the PCB
2022-10-14 Added stitching vias
2022-10-17 Finished adding stitching vias to the PCB
2022-10-19 Started sourcing parts from digikey, got to part 15, corrected mistakes as I go along
2022-10-21 Finished digi-key BOM and made appropriate changes to schematic and PCB
2022-11-18 Updated BOM
2023-02-10 Corrected LT1054 -5V power output label placement, identified which components are 0201 and corrected digi number and page of C-47,48,49,52,53,58 1u caps
2023-02-19 Sourced 0603 replacements for 0201 components
2023-02-19 Re-organized Sub-bass and Bass part of the PCB
2023-03-01 Changed 0603 footprint to hand solder version, and changed 0402 footprints to 0603 hand solder version
2023-03-02 Corrected Resistor footprints from Capacitor_SMD to Resistor_SMD and created BOM
2023-03-15 Corrected Spectrum Filter mistakes
    In Kicad, op amp filters were connected as positive feedback, changed to negative feedback; corrected R5 and R8 values in FinalLowMidrange LTSpice file; corrected R2 and R3 in FinalUpperMidrange LTsp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
2023-07-21 Add mounting holes and adjust component placement as necessary
2023-07-21 placed the power jack and audio jack slightly over the border of the PCB for an easier connection
2023-08-02 Change value of R82 (9V power indicator) from 330 ohms to 620 ohms
2023-08-02 Labeled output of U17 (3.5V LDO) 3.5V
2023-08-03 Moved R82 closer to the power LED
2023-08-03 Added new BOM Music_Visualizer_BOM_Digikey_Final_V2
2023-08-04 Verified BOM correctness and availabity of parts
2023-09-14 Simulated Filters with a voltage follower (buffer) prepended to it, and with all filters in the same simulation; one with the buffered version, one with the non-buffered version, and one with both ve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
2023-09-14 Added 4th op amp in each LM324 IC as a voltage follower (buffer) for each spectrum filter in the schematic
2023-09-14 Added and connected buffers in the PCB
2023-09-14 Rotate silkscreen for C47, C48 and C49
2023-09-14 Added grounding Vias
2023-09-14 Added one more grounding via
2023-09-14 Ran DRC, no more errors
2023-09-14 Made a BOM of only the passive SMD devices
2023-10-02 Added audio output source resistance of 73 ohms
2023-10-02 Ran various experiments
2023-10-25 Re-oriented C55 (The 100uF capacitor) so that the positive terminal is connected to ground and the negative terminal is connected to -5V in the schematic and PCB layout
2023-10-27 Used an emitter follower circuit to replace the unity voltage buffer in the Rhi control circuit
2023-11-03 Measured the frequency response, and calculated the value of the volumeter
2023-12-30 Place Spectrum_Filters in simulated_circuits folder, and deleted Combined_Final
2023-12-30 Place Spectrum_Filters in simulated_circuits folder, and deleted Combined_Final again
2023-12-30 Moved RhiControl_LTC1250 to LED_Driving folder, and added comment for power conneciton rational
2023-12-30 Move LM3915_Base_CircuitV3 and LM3915_Chan_Adj_Ground to LED_Driving
2023-12-30 Shortened name by removing V3 again
2023-12-30 Shortened name by removing _Adj_Ground
2023-12-31 Removed Ad_hoc folder
2023-12-31 Move Entire_Circuit and Filters_With_LED_Drivers to Simulated_Circuits
2023-12-31 Rename FrequencyInformation to Sound_Characterization, and add Driver_Volume_Meter to that excel file
2024-01-01 Update README.md
    Wrote high-level overview of the project
2024-01-01 Update README.md
    Complete Overview
2024-01-04 Update README.md
    Corrected spelling mistakes in Overview
2024-01-04 Update README.md
    Started making file structure
2024-01-04 Update README.md
    Add all folders to Repository structure
2024-01-04 Removed BOM.txt and DC_Jack.pretty from Music_Visualize/Project_Library/DC_Power_Jack
2024-01-04 Delte all .log and .raw files from Power Sub-folder
2024-01-05 Update README.md
    Finished showing overall file strucutr
2024-01-05 Update README.md
    Document and explanation of schematic and PCB file explanation
2024-01-05 Change signal input from superdiode to a simple AC voltage source
2024-01-05 Update README.md
    Added Schematic_PCB\Music_Visualizer and started adding the Simulated circuits to the Folder explanation section
2024-01-05 Update README.md
    Bolded names of files/folders in folder section
2024-01-05 Remove Real_Filters directory
2024-01-05 remove Final_No_Buffer directory
2024-01-05 Update README.md
    Removed Final_No_Buffer and Real_Filters directories
2024-01-06 Moved files from Final_with_Buffer to Final_Filters and delete Final_with_Buffer
2024-01-06 Update README.md
    Complete Spectrum Filter Section
2024-01-06 Update README.md
    Bolded the colons
2024-01-06 Update README.md
    Changed 4. to Folder and Design File Explantion
2024-01-06 Update README.md
    Updated repository structure
2024-01-06 Update README.md
    Changed heading type for Table of Contents, Summary of Functionality, and Contained in Respository
2024-01-06 Moved DC power jack symbol from global library to project specific library
2024-01-06 Update README.md
    Add more content to Music_Visualizer.kicad_sch explanation!
2024-01-06 Update README.md
    Add Generate Files for Fabrication, Current Issues and Acknowledgments
2024-01-06 Update README.md
    Added License
2024-01-09 Added 3D modles for blue, red and yellow 5mm cutted opaque LEDS and used their 3D models for the project
2024-01-10 Update README.md
    Add block diagram
2024-01-13 Update README.md
    Added more images
2024-01-23 Lowered font of Diode value (the name - NSCW100) to 1.0
2024-01-23 Update README.md
    New base driver picture, made diode name of diode smaller, Vrhi now set by constant voltage source, adjusted explanation of circuit to reflect this
2024-01-23 Rearraged Power circuitry schematic and made the paper size custom: 180W x 250H
2024-01-23 Update README.md
    New rearranged power circuitry schematic
2024-01-23 Update README.md
    Added Coloured_LEDs to file structure, and properly aligned DC_Power_Jack
2024-02-04 Update README.md
    Labelled figure 1 and 2
2024-02-04 Update README.md
    Captioned all images, made figure 5 bigger
2024-02-04 Update README.md
    Modified file explanations
